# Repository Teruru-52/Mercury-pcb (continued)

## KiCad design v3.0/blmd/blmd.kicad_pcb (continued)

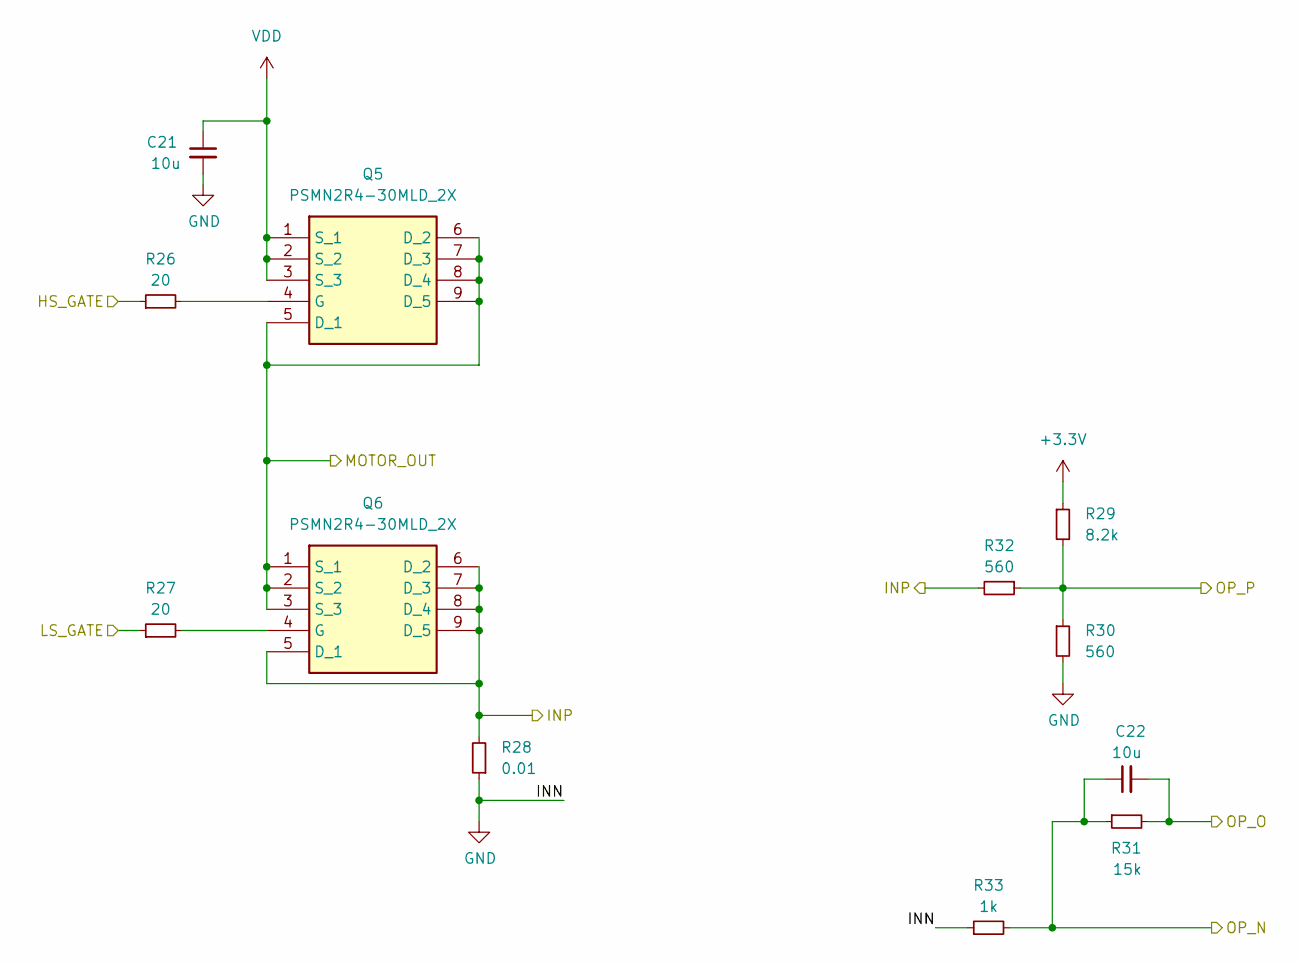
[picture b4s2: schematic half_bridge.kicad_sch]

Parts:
C21: 10u; C_0805_2012Metric
C22: 10u; C_0402_1005Metric
Q5, Q6: PSMN2R4-30MLD_2X; PSMN02030MLCX; Manufacturer_Part_Number PSMN2R4-30MLD/2X
R26, R27: 20; R_0402_1005Metric
R28: 0.01; R_0805_2012Metric
R29: 8.2k; R_0201_0603Metric
R30, R32: 560; R_0201_0603Metric
R31: 15k; R_0201_0603Metric
R33: 1k; R_0201_0603Metric

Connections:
+3.3V: R29.1; also elsewhere on the board
/HSW: R26.1; also elsewhere on the board
/LSW: R27.1; also elsewhere on the board
/OP_3N: C22.1, R31.1, R33.2; also elsewhere on the board
/OP_3O: C22.2, R31.2; also elsewhere on the board
/OP_3P: R29.2, R30.1, R32.1; also elsewhere on the board
/OUTW: Q5.5 (D_1), Q5.6 (D_2), Q5.7 (D_3), Q5.8 (D_4), Q5.9 (D_5), Q6.1 (S_1), Q6.2 (S_2), Q6.3 (S_3); also elsewhere on the board
/half_bridge2/INP: Q6.5 (D_1), Q6.6 (D_2), Q6.7 (D_3), Q6.8 (D_4), Q6.9 (D_5), R28.2, R32.2; also elsewhere on the board
GND: C21.2, R28.1, R30.2, R33.1; also elsewhere on the board
unnamed: Q5.4 (G), R26.2
unnamed: Q6.4 (G), R27.2
VDD: C21.1, Q5.1 (S_1), Q5.2 (S_2), Q5.3 (S_3); also elsewhere on the board

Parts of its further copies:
C17, C19: 10u; C_0805_2012Metric
C18, C20: 10u; C_0402_1005Metric
Q1, Q2, Q3, Q4: PSMN2R4-30MLD_2X; PSMN02030MLCX; Manufacturer_Part_Number PSMN2R4-30MLD/2X
R10, R11, R18, R19: 20; R_0402_1005Metric
R12, R20: 0.01; R_0805_2012Metric
R13, R21: 8.2k; R_0201_0603Metric
R14, R16, R22, R24: 560; R_0201_0603Metric
R15, R23: 15k; R_0201_0603Metric
R17, R25: 1k; R_0201_0603Metric

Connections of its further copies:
+3.3V: R13.1, R21.1; also elsewhere on the board
/HSU: R18.1; also elsewhere on the board
/HSV: R10.1; also elsewhere on the board
/LSU: R19.1; also elsewhere on the board
/LSV: R11.1; also elsewhere on the board
/OP_1N: C20.1, R23.1, R25.2; also elsewhere on the board
/OP_1O: C20.2, R23.2; also elsewhere on the board
/OP_1P: R21.2, R22.1, R24.1; also elsewhere on the board
/OP_2N: C18.1, R15.1, R17.2; also elsewhere on the board
/OP_2O: C18.2, R15.2; also elsewhere on the board
/OP_2P: R13.2, R14.1, R16.1; also elsewhere on the board
/OUTU: Q3.5 (D_1), Q3.6 (D_2), Q3.7 (D_3), Q3.8 (D_4), Q3.9 (D_5), Q4.1 (S_1), Q4.2 (S_2), Q4.3 (S_3); also elsewhere on the board
/OUTV: Q1.5 (D_1), Q1.6 (D_2), Q1.7 (D_3), Q1.8 (D_4), Q1.9 (D_5), Q2.1 (S_1), Q2.2 (S_2), Q2.3 (S_3); also elsewhere on the board
/half_bridge1/INP: Q2.5 (D_1), Q2.6 (D_2), Q2.7 (D_3), Q2.8 (D_4), Q2.9 (D_5), R12.2, R16.2
/half_bridge/INP: Q4.5 (D_1), Q4.6 (D_2), Q4.7 (D_3), Q4.8 (D_4), Q4.9 (D_5), R20.2, R24.2
GND: C17.2, C19.2, R12.1, R14.2, R17.1, R20.1, R22.2, R25.1; also elsewhere on the board
unnamed: Q1.4 (G), R10.2
unnamed: Q2.4 (G), R11.2
unnamed: Q3.4 (G), R18.2
unnamed: Q4.4 (G), R19.2
VDD: C17.1, C19.1, Q1.1 (S_1), Q1.2 (S_2), Q1.3 (S_3), Q3.1 (S_1), Q3.2 (S_2), Q3.3 (S_3); also elsewhere on the board

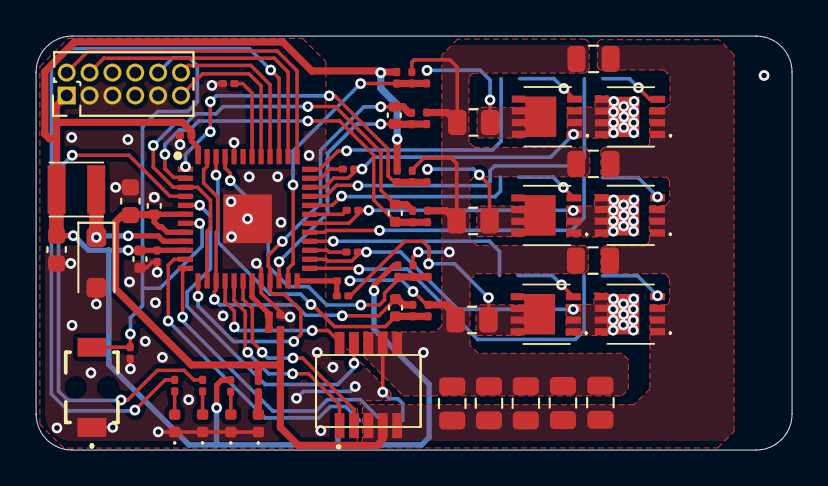
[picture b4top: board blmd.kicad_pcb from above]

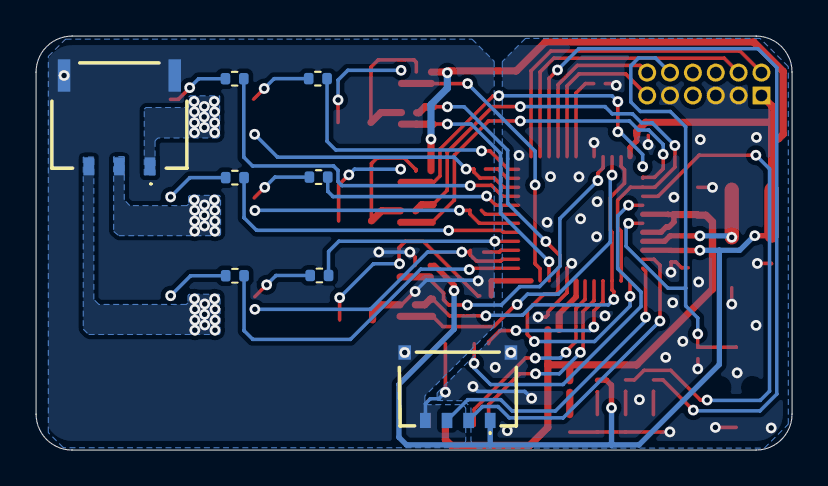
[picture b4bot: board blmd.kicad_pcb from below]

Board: 2 copper layers, 42.0 x 23.0 mm, 72 parts (8 on the bottom side), 54 nets.

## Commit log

2025-02-25 chore: add pcb files
